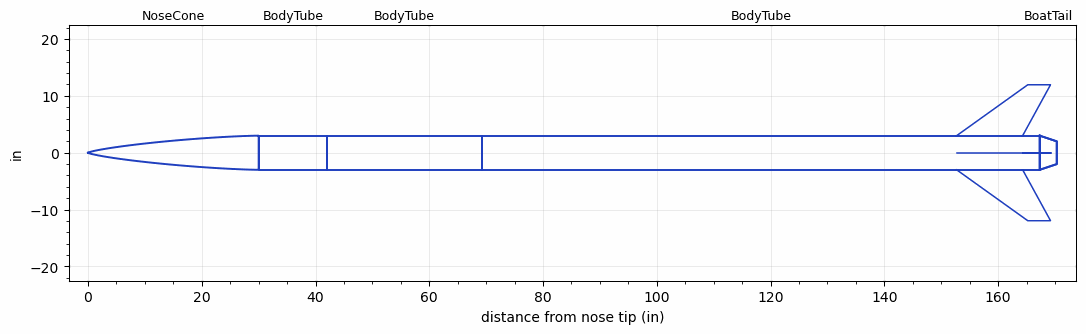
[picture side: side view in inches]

<RASAeroDocument>
 <FileVersion>2</FileVersion>
 <RocketDesign>
  <NoseCone>
   <Length>29.9999</Length>
   <Diameter>6</Diameter>
   <Shape>Von Karman Ogive</Shape>
   <Location>0</Location>
  </NoseCone>
  <BodyTube>
   <Length>12</Length>
   <Diameter>6</Diameter>
   <Location>29.9999</Location>
  </BodyTube>
  <BodyTube>
   <Length>27.2579</Length>
   <Diameter>6</Diameter>
   <Location>41.9999</Location>
  </BodyTube>
  <BodyTube>
   <Length>98.0598</Length>
   <Diameter>6</Diameter>
   <Location>69.2579</Location>
   <BoattailLength>3</BoattailLength>
   <BoattailRearDiameter>4</BoattailRearDiameter>
   <Fin>
    <Count>4</Count>
    <Chord>11.6</Chord>
    <Span>8.95</Span>
    <SweepDistance>12.5</SweepDistance>
    <TipChord>4</TipChord>
    <Thickness>0.3</Thickness>
    <Location>14.6</Location>
    <AirfoilSection>Subsonic NACA</AirfoilSection>
   </Fin>
  </BodyTube>
  <BoatTail>
   <Length>3</Length>
   <Diameter>6</Diameter>
   <RearDiameter>4</RearDiameter>
   <Location>167.3177</Location>
  </BoatTail>
  <Surface>Camouflage Paint</Surface>
  <ModifiedBarrowman>False</ModifiedBarrowman>
  <Turbulence>False</Turbulence>
  <UseBooster1>False</UseBooster1>
  <UseBooster2>False</UseBooster2>
  <Comments>2027 IREC rocket Preliminary design - 10/08/2026</Comments>
 </RocketDesign>
 <LaunchSite>
  <Altitude>0</Altitude>
  <Pressure>27.0701</Pressure>
  <RodAngle>8</RodAngle>
  <RodLength>32.8</RodLength>
  <Temperature>76</Temperature>
  <WindSpeed>18</WindSpeed>
 </LaunchSite>
 <Recovery>
  <Altitude1>0</Altitude1>
  <Altitude2>0</Altitude2>
  <DeviceType1>None</DeviceType1>
  <DeviceType2>None</DeviceType2>
  <Event1>False</Event1>
  <Event2>False</Event2>
  <Size1>0</Size1>
  <Size2>0</Size2>
  <EventType1>None</EventType1>
  <EventType2>None</EventType2>
  <CD1>0</CD1>
  <CD2>0</CD2>
 </Recovery>
 <SimulationList>
  <Simulation>
   <SustainerEngine>ENGINE-2027-python-og  (TAMUSRT)</SustainerEngine>
   <SustainerLaunchWt>133.53</SustainerLaunchWt>
   <SustainerNozzleDiameter>4</SustainerNozzleDiameter>
   <SustainerCG>107.59</SustainerCG>
   <SustainerIgnitionDelay>0</SustainerIgnitionDelay>
   <Booster1SeparationDelay>0</Booster1SeparationDelay>
   <Booster1IgnitionDelay>0</Booster1IgnitionDelay>
   <IncludeBooster1>False</IncludeBooster1>
   <Booster2Delay>0</Booster2Delay>
   <IncludeBooster2>False</IncludeBooster2>
   <TimetoApogee>43.64868</TimetoApogee>
   <MaxAltitude>30183.66</MaxAltitude>
   <MaxVelocity>1879.657</MaxVelocity>
  </Simulation>
  <Simulation>
   <SustainerEngine>Thrust-Trade-1  (TAMUSRT)</SustainerEngine>
   <SustainerLaunchWt>133.53</SustainerLaunchWt>
   <SustainerNozzleDiameter>4</SustainerNozzleDiameter>
   <SustainerCG>107.59</SustainerCG>
   <SustainerIgnitionDelay>0</SustainerIgnitionDelay>
   <Booster1SeparationDelay>0</Booster1SeparationDelay>
   <Booster1IgnitionDelay>0</Booster1IgnitionDelay>
   <IncludeBooster1>False</IncludeBooster1>
   <Booster2Delay>0</Booster2Delay>
   <IncludeBooster2>False</IncludeBooster2>
   <TimetoApogee>45.50837</TimetoApogee>
   <MaxAltitude>34606.14</MaxAltitude>
   <MaxVelocity>1898.757</MaxVelocity>
  </Simulation>
  <Simulation>
   <SustainerEngine>Thrust-Trade-4500  (TAMUSRT)</SustainerEngine>
   <SustainerLaunchWt>133.53</SustainerLaunchWt>
   <SustainerNozzleDiameter>4</SustainerNozzleDiameter>
   <SustainerCG>107.59</SustainerCG>
   <SustainerIgnitionDelay>0</SustainerIgnitionDelay>
   <Booster1SeparationDelay>0</Booster1SeparationDelay>
   <Booster1IgnitionDelay>0</Booster1IgnitionDelay>
   <IncludeBooster1>False</IncludeBooster1>
   <Booster2Delay>0</Booster2Delay>
   <IncludeBooster2>False</IncludeBooster2>
   <TimetoApogee>46.14826</TimetoApogee>
   <MaxAltitude>34870.22</MaxAltitude>
   <MaxVelocity>1877.472</MaxVelocity>
  </Simulation>
  <Simulation>
   <SustainerEngine>Thrust-Trade-4000  (TAMUSRT)</SustainerEngine>
   <SustainerLaunchWt>133.53</SustainerLaunchWt>
   <SustainerNozzleDiameter>4</SustainerNozzleDiameter>
   <SustainerCG>107.59</SustainerCG>
   <SustainerIgnitionDelay>0</SustainerIgnitionDelay>
   <Booster1SeparationDelay>0</Booster1SeparationDelay>
   <Booster1IgnitionDelay>0</Booster1IgnitionDelay>
   <IncludeBooster1>False</IncludeBooster1>
   <Booster2Delay>0</Booster2Delay>
   <IncludeBooster2>False</IncludeBooster2>
   <TimetoApogee>46.74816</TimetoApogee>
   <MaxAltitude>34904.87</MaxAltitude>
   <MaxVelocity>1842.321</MaxVelocity>
  </Simulation>
  <Simulation>
   <SustainerEngine>Thrust-Trade-3500  (TAMUSRT)</SustainerEngine>
   <SustainerLaunchWt>135.07</SustainerLaunchWt>
   <SustainerNozzleDiameter>4</SustainerNozzleDiameter>
   <SustainerCG>107.24</SustainerCG>
   <SustainerIgnitionDelay>0</SustainerIgnitionDelay>
   <Booster1SeparationDelay>0</Booster1SeparationDelay>
   <Booster1IgnitionDelay>0</Booster1IgnitionDelay>
   <IncludeBooster1>False</IncludeBooster1>
   <Booster2Delay>0</Booster2Delay>
   <IncludeBooster2>False</IncludeBooster2>
   <TimetoApogee>47.35806</TimetoApogee>
   <MaxAltitude>34338.93</MaxAltitude>
   <MaxVelocity>1780.492</MaxVelocity>
  </Simulation>
  <Simulation>
   <SustainerEngine>Thrust-Trade-3000  (TAMUSRT)</SustainerEngine>
   <SustainerLaunchWt>135.07</SustainerLaunchWt>
   <SustainerNozzleDiameter>4</SustainerNozzleDiameter>
   <SustainerCG>107.24</SustainerCG>
   <SustainerIgnitionDelay>0</SustainerIgnitionDelay>
   <Booster1SeparationDelay>0</Booster1SeparationDelay>
   <Booster1IgnitionDelay>0</Booster1IgnitionDelay>
   <IncludeBooster1>False</IncludeBooster1>
   <Booster2Delay>0</Booster2Delay>
   <IncludeBooster2>False</IncludeBooster2>
   <TimetoApogee>48.10793</TimetoApogee>
   <MaxAltitude>33499.62</MaxAltitude>
   <MaxVelocity>1730.013</MaxVelocity>
  </Simulation>
 </SimulationList>
</RASAeroDocument>
